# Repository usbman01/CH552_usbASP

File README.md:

# CH552_usbASP

A CH552 version of the popular usbasp from fischl. The code is mostly based on version 1.8 of nerdralph https://github.com/nerdralph/usbasp with some minor changes, exept for tpi.c and usbdrv.c which are completely new. It will work on the following WCH microcontroller:

  - CH551 (needs some changes because of XDATA limits)
  - CH552
  - CH554

CH552_usbasp is much more stable because it no longer depends on VUSB. On windows machines it can automatically load winusb as driver so no more installation issues and hassles with zadig. If there is already a usbasp installation on the PC with libusb, libusb will be used. On Linux always libusb will be used because WCID is windows only.

## Features:

  - Fullspeed (12MHz) design
  - Firmware update via USB using WCHs WCHISPTool 
  - Automatic driver installation on Win8.1 and above
  - Winusb driver (tested with avrDude >= 7.1)
  - Compound device with USB CDC-ACM serial port 
  - 5V and 3.3V operation

## Config Options:

WCID, TPI, CDC and the fast copy function can be switched off. For details check global.h The code can be compiled using Keil c51, SDCC or Raisonance rc51. A port to IAR EW8051 is still under develpment and currently not working.   
Since i dont have AVRs using TPI at hand TPI is just simulated and may or may not work. 

## Benchmarks:

Since the code is prepared to work with various C compiler it also can be used for benchmarking popular MCS51 C compiler. 

## Limits:

When using the compound version including CDC its neccessary to use avrdude-v8.0-windows-mingw-x64.zip because the normal version can not handle compount devices.

## todo:

 - make usbdrv usb2cv compilant
 - complete CDC support
 - switch to 24MHz fsys so CDC can work up to 115k2 baud
 - complete SDCC support (build) ✔
 - use that extra opcode for memcpy functions ✔
 - add Raisonance RC51 support ✔
 - complete IAR EW8051 support

## References:

 - Datasheet:  https://www.wch-ic.com/downloads/CH552DS1_PDF.html
 - Isptool:    https://www.wchic.com/downloads/WCHISPTool_Setup_exe.html
 - usbasp 1.4: https://www.fischl.de/usbasp/
 - usbasp 1.8: https://github.com/nerdralph/usbasp
 - avrdude:    https://github.com/avrdudes/avrdude/releases

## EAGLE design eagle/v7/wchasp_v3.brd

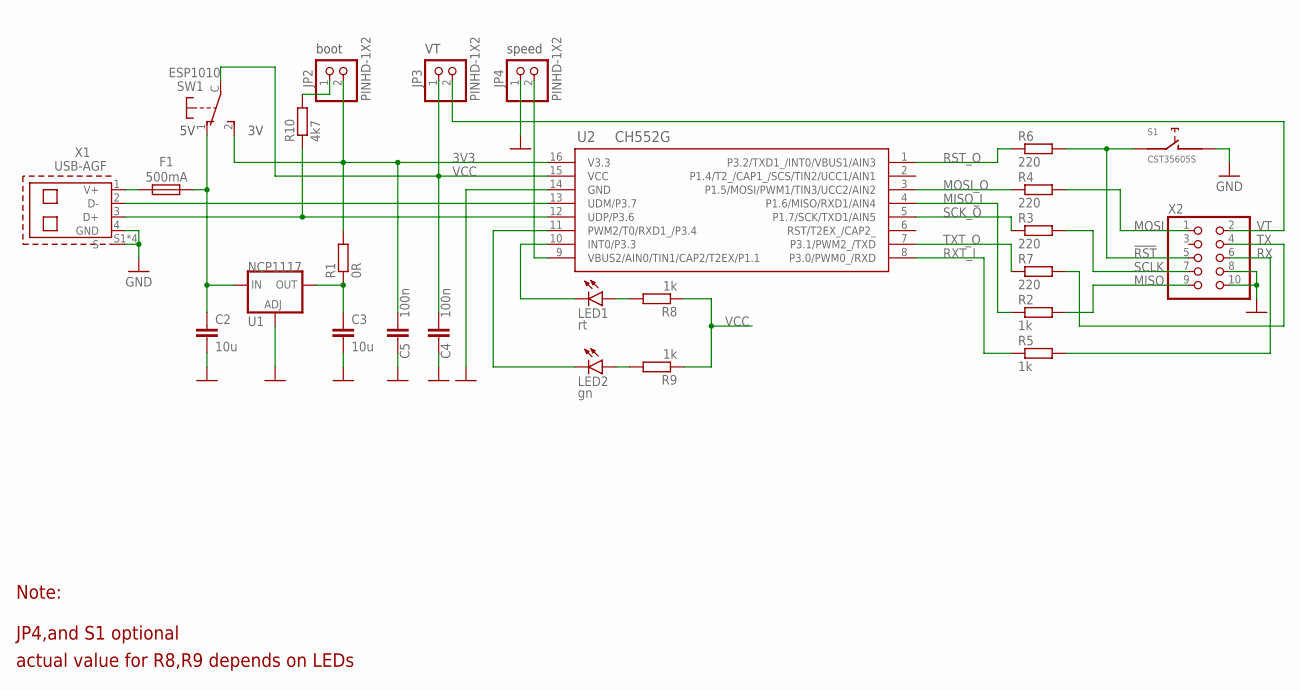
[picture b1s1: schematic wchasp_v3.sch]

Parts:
C2, C3: 10u; C0805K
C4, C5: 100n; C0603
F1: 500mA; R0805W
JP2, JP3, JP4: PINHD-1X2; 1X2
LED1: rt; D0603
LED2: gn; D0603
R1: 0R; R0603
R2, R5, R8, R9: 1k; R0603
R3, R4, R6, R7: 220; R0603
R10: 4k7; R0603
S1: CST35605S
SW1: ESP1010
U1: NCP1117; SOT223
U2: CH552G; SO16
X1: USB-AGF
X2: PINHD-2X5/90; 2X05/90

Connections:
3V3: C5.1, JP2.2, R1.2, SW1.2 (S), U2.16 (V3.3)
!RST: R6.2, S1.1, X2.5
GND: C2.2, C3.2, C4.2, C5.2, JP4.1, S1.2, U1.1 (ADJ), U2.14 (GND), X1.4 (GND), X1.S1 (S), X1.S2 (S), X1.S3 (S), X1.S4 (S), X2.8, X2.10
MISO: R2.2, X2.9
MISO_I: R2.1, U2.4 (P1.6/MISO/RXD1/AIN4)
MOSI: R4.2, X2.1
MOSI_O: R4.1, U2.3 (P1.5/MOSI/PWM1/TIN3/UCC2/AIN2)
unnamed: JP2.1, R10.2
unnamed: U2.13 (UDM/P3.7), X1.2 (D-)
unnamed: R10.1, U2.12 (UDP/P3.6), X1.3 (D+)
unnamed: LED1.A, R8.2
unnamed: C2.1, F1.2, SW1.1 (O), U1.3 (IN)
unnamed: C3.1, R1.1, U1.2 (OUT), U1.4 (OUT)
unnamed: LED2.A, R9.2
unnamed: LED2.K (C), U2.11 (PWM2/T0/RXD1_/P3.4)
unnamed: LED1.K (C), U2.10 (INT0/P3.3)
unnamed: F1.1, X1.1 (V+)
RST_O: R6.1, U2.1 (P3.2/TXD1_/INT0/VBUS1/AIN3)
RX: R5.2, X2.6
RXT_I: R5.1, U2.8 (P3.0/PWM0_/RXD)
SCK_O: R3.1, U2.5 (P1.7/SCK/TXD1/AIN5)
SCLK: R3.2, X2.7
SLOW: JP4.2, U2.9 (VBUS2/AIN0/TIN1/CAP2/T2EX/P1.1)
TX: R7.2, X2.4
TXT_O: R7.1, U2.7 (P3.1/PWM2_/TXD)
VCC: C4.1, JP3.1, R8.1, R9.1, SW1.C, U2.15 (VCC)
VT: JP3.2, X2.2

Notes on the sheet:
boot
speed
JP4,and S1 optional
actual value for R8,R9 depends on LEDs
Note:

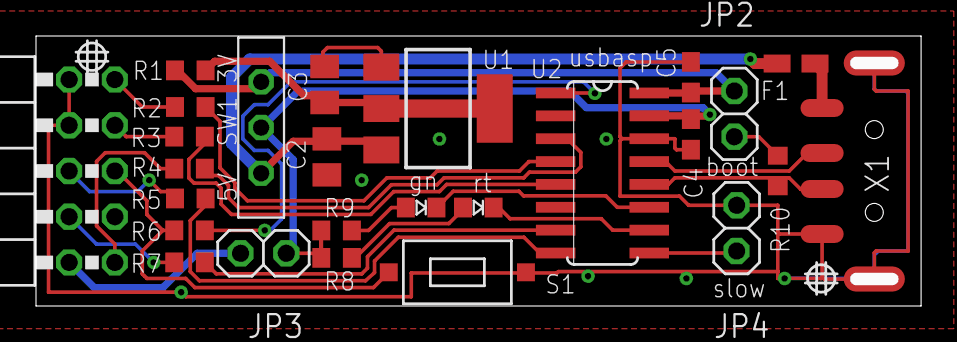
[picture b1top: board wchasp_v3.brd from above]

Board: 2 copper layers, 48.5 x 14.3 mm, 28 parts (0 on the bottom side), 27 nets.

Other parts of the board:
U$1, U$2: CENTER

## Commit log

2024-12-15 initial
2024-12-19 SDCC fix
2025-01-11 changes for rc51
2025-01-11 SDCC + rc51 complete
